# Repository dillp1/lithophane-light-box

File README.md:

# Lithophane Light Box

Battery-powered light boxes for displaying 3D-printed lithophanes, built as handmade holiday gifts.
A lithophane is a thin print that shows a photo when it's lit from behind; this board provides
an even backlight from a row of LEDs, and a 3D-printed base hides the board, battery pack and switch.

## The board

A two-layer, all through-hole PCB designed in KiCad so it can be soldered by hand.

| Qty | Part | Footprint |
| --- | --- | --- |
| 25 | 5 mm LED | LED_D5.0mm |
| 25 | 300 Ω resistor (one per LED) | Axial, DIN0207 |
| 1 | 2-pin header, for the battery pack and switch | 2.54 mm pitch |

## Files

| Folder | Contents |
| --- | --- |
| `kicad/` | KiCad project, schematic and PCB layout |
| `fabrication/` | Gerbers, drill files, BOM and pick-and-place files as sent to PCBWay |

## Ordering a board

Upload `fabrication/lithophaneLED-gerbers-PCBWay.zip` to PCBWay or any other PCB manufacturer.

## Author

Dillon Michlena · [GitHub](https://github.com/dillp1)

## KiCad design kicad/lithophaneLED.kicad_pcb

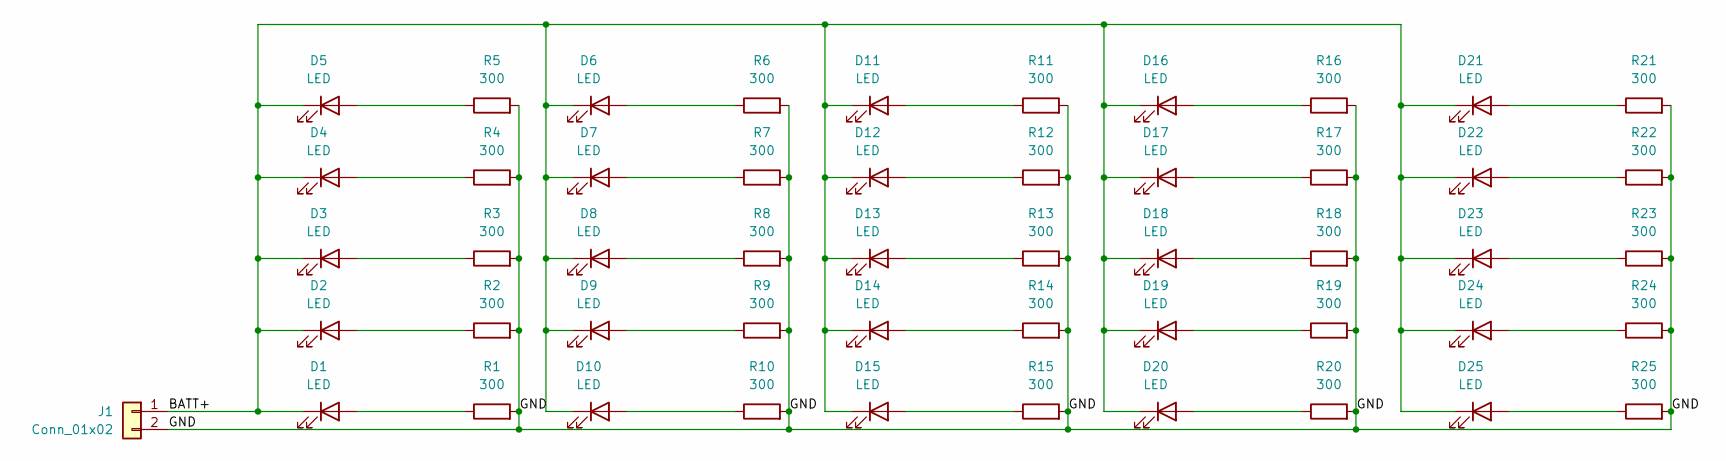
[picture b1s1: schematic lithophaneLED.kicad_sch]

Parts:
D1, D2, D3, D4, D5, D6, D7, D8, D9, D10, D11, D12, D13, D14, D15, D16, D17, D18, D19, D20, D21, D22, D23, D24, D25: LED; LED_D5.0mm
J1: Conn_01x02; PinHeader_1x02_P2.54mm_Horizontal
R1, R2, R3, R4, R5, R6, R7, R8, R9, R10, R11, R12, R13, R14, R15, R16, R17, R18, R19, R20, R21, R22, R23, R24, R25: 300; R_Axial_DIN0207_L6.3mm_D2.5mm_P7.62mm_Horizontal

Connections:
/BATT+: D1.1 (K), D2.1 (A), D3.1 (K), D4.1 (K), D5.1 (K), D6.1 (K), D7.1 (K), D8.1 (K), D9.1 (K), D10.1 (K), D11.1 (K), D12.1 (K), D13.1 (K), D14.1 (K), D15.1 (K), D16.1 (K), D17.1 (K), D18.1 (K), D19.1 (K), D20.1 (K), D21.1 (K), D22.1 (K), D23.1 (K), D24.1 (K), D25.1 (K), J1.1
/GND: J1.2, R1.2, R2.2, R3.2, R4.2, R5.2, R6.2, R7.2, R8.2, R9.2, R10.2, R11.2, R12.2, R13.2, R14.2, R15.2, R16.2, R17.2, R18.2, R19.2, R20.2, R21.2, R22.2, R23.2, R24.2, R25.2
unnamed: D1.2 (A), R1.1
unnamed: D2.2 (K), R2.1
unnamed: D3.2 (A), R3.1
unnamed: D4.2 (A), R4.1
unnamed: D5.2 (A), R5.1
unnamed: D6.2 (A), R6.1
unnamed: D7.2 (A), R7.1
unnamed: D8.2 (A), R8.1
unnamed: D9.2 (A), R9.1
unnamed: D10.2 (A), R10.1
unnamed: D11.2 (A), R11.1
unnamed: D12.2 (A), R12.1
unnamed: D13.2 (A), R13.1
unnamed: D14.2 (A), R14.1
unnamed: D15.2 (A), R15.1
unnamed: D16.2 (A), R16.1
unnamed: D17.2 (A), R17.1
unnamed: D18.2 (A), R18.1
unnamed: D19.2 (A), R19.1
unnamed: D20.2 (A), R20.1
unnamed: D21.2 (A), R21.1
unnamed: D22.2 (A), R22.1
unnamed: D23.2 (A), R23.1
unnamed: D24.2 (A), R24.1
unnamed: D25.2 (A), R25.1

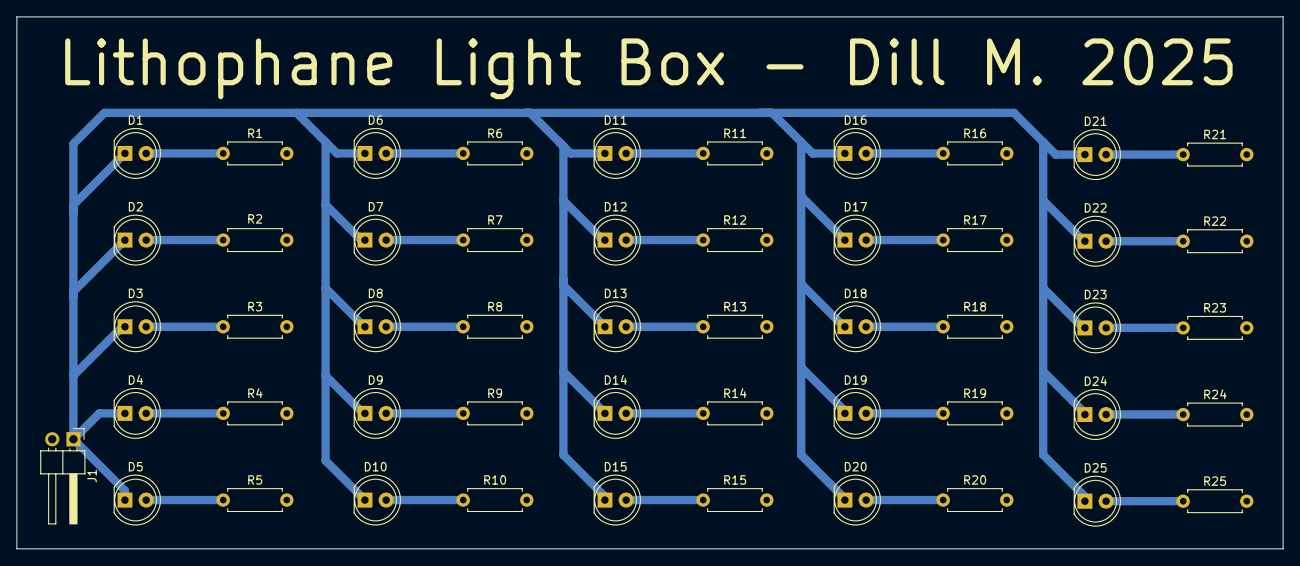
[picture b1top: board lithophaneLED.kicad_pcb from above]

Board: 2 copper layers, 151.8 x 63.8 mm, 51 parts (0 on the bottom side), 27 nets.
